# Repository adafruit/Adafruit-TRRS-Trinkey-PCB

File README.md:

## Adafruit TRRS Trinkey - USB Key for Assistive Technology PCB

<a href="http://www.adafruit.com/products/5954"><br/>
Click here to purchase one from the Adafruit shop</a>

PCB files for the Adafruit TRRS Trinkey - USB Key for Assistive Technology. 

Format is EagleCAD schematic and board layout
* https://www.adafruit.com/product/5954

### Description

It's half USB Key, half TRRS breakout... it's the Adafruit TRRS Trinkey specifically designed for Assistive Technology hackers and creators as a simple and low cost, but also flexible and extendable AT device. 

Many AT interface devices use 3.5mm audio jacks to create switches or variable inputs - often mono TS or stereo TRS plugs. On the TRRS Trinkey, we connect all 6 pins of a 'switched' TRRS jack - tip, ring 1, ring 2, sleeve and the tip switch plus ring 1 switch - to 6 GPIO pins on the microcontroller. That means we can not only detect when plugs are inserted but can change which pins are input, ground or even 3V power. With the use of a stereo/mic splitter, we can have up to 3 simple switches, or two analog potentiometers, or one of each! We particularly like this jack because it has two through-hole contacts near the opening for a good mechanical connection.

The PCB is designed to plug into any USB A port on a computer or laptop. There's an ATSAMD21 microcontroller on board with just enough circuitry to keep it happy. One pin of the microcontroller connects to a NeoPixel LED. A reset button lets you enter bootloader mode if necessary. The microcontroller can be programmed easily thanks to the UF2 bootloader and CircuitPython: simply drag-n-drop new code on.

The SAMD21 can run CircuitPython or Arduino nicely. Over the USB connection, you can have serial, MIDI, or HID keyboard/mouse connectivity. Because its a fully programmable chip, it's possible to customize the keyboard or mouse commands executed on each button, or even set up chording patterns.

Features:

* ATSAMD21E18 32-bit Cortex M0+ - 48 MHz 32-bit processor with 256KB Flash and 32 KB RAM
* Native USB supported by every OS - can be used in Arduino or CircuitPython as a USB serial console, MIDI, Keyboard/Mouse HID, and even a little disk drive for storing Python scripts. Can act like a keyboard to phones or tablets with a USB adapter cable.
* Can be used with Arduino IDE or CircuitPython
* TRRS Jack with two switches on tip and ring 1. All 6 contacts connect to analog-input capable GPIO pins
* One RGB NeoPixel LED
* STEMMA QT port with JST SH 4-pin compatible connector - can be used to add I2C devices, or two more inputs. Note CircuitPython may not have enough memory for large chip drivers.
* Reset switch to start your project code over or enter bootloader mode
* Open Source Hardware so you have full control over your assistive tech!

### License

Adafruit invests time and resources providing this open source design, please support Adafruit and open-source hardware by purchasing products from [Adafruit](https://www.adafruit.com)!

Designed by Limor Fried/Ladyada for Adafruit Industries.

Creative Commons Attribution/Share-Alike, all text above must be included in any redistribution. 
See license.txt for additional details.

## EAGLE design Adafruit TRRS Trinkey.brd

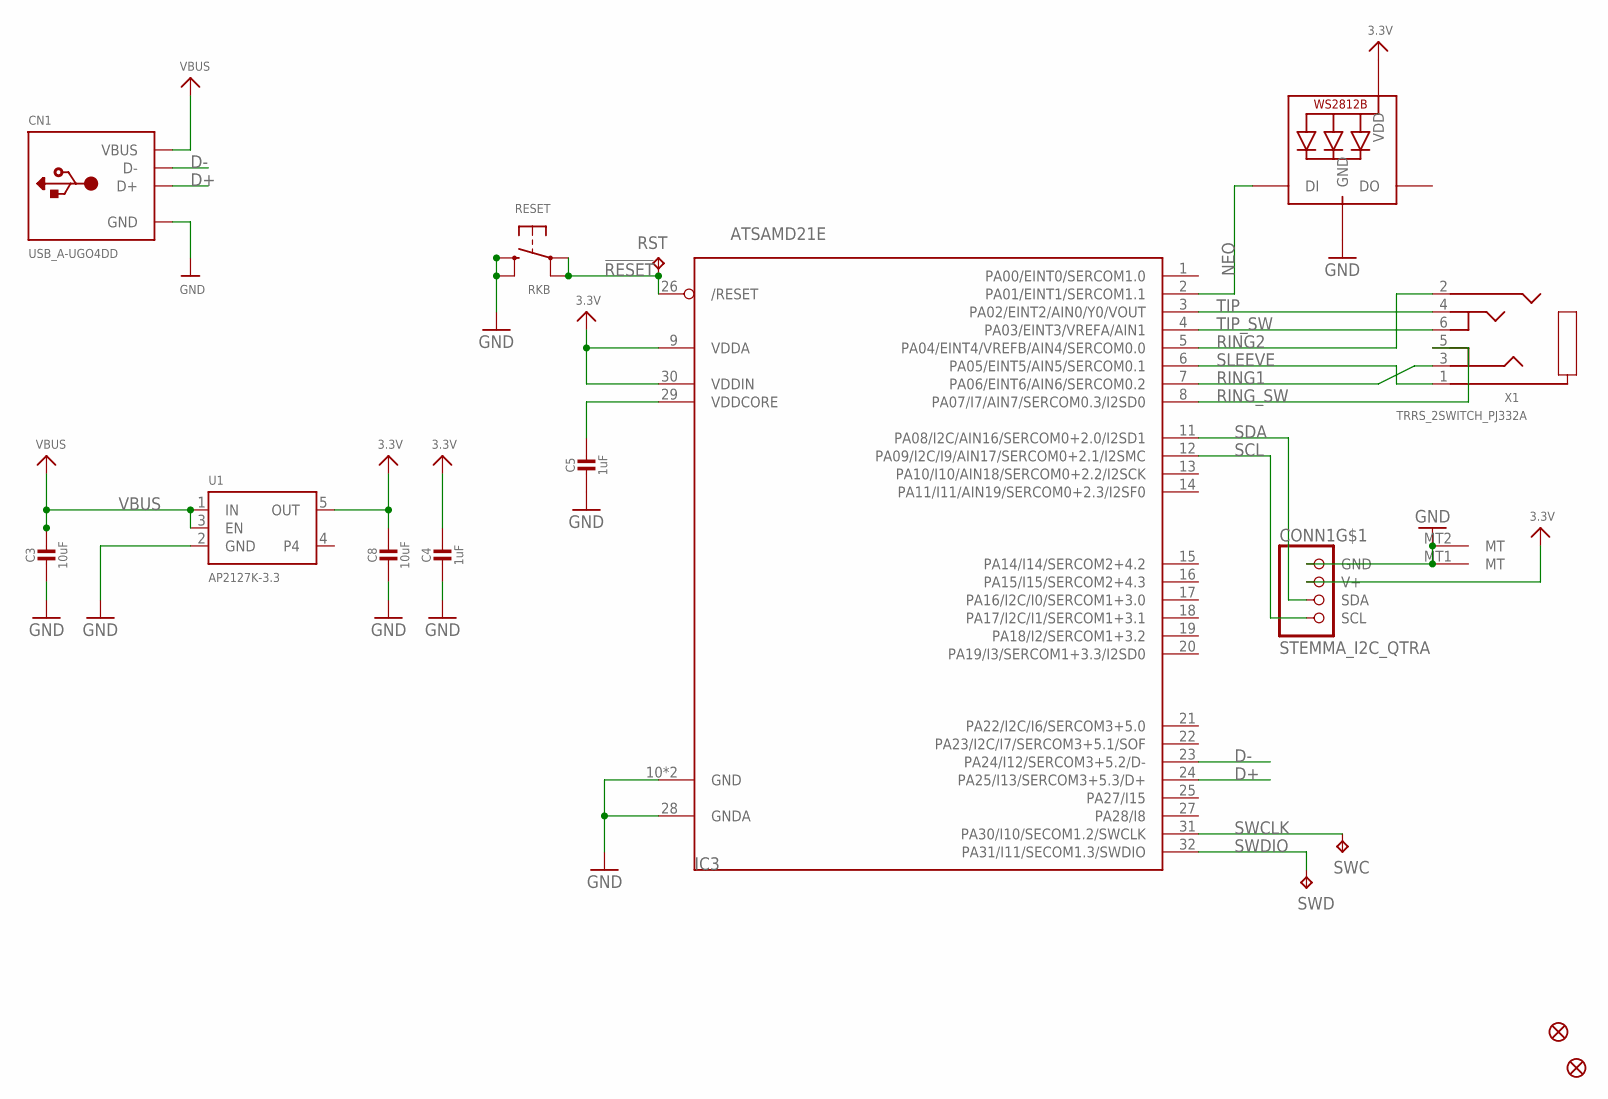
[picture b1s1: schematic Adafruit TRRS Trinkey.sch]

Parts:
C3, C8: 10uF; 0805-NO
C4, C5: 1uF; 0603-NO
CN1: USB_A-UGO4DD
CONN1: STEMMA_I2C_QTRA; JST_SH4_RA
FID1, FID2: FIDUCIAL_0.5MM
IC3: ATSAMD21E; QFN32_5MM
LED1: WS2812B_SK6805_1515; SK6805_1515
RESET: RKB; BTN_RKB2_4.6X2.8
RST: TPTP16R; TP16R
SWC: TPTP15R; TP15R
SWD: TPTP16R; TP16R
U1: AP2127K-3.3; SOT23-5; JLC_ROTATION 0
X1: TRRS_2SWITCH_PJ332A; PJ-332A

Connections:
3.3V: C4.1, C8.1, CONN1.2 (V+), IC3.9 (VDDA), IC3.30 (VDDIN), LED1.2 (VDD), U1.5 (OUT)
!RESET: IC3.26 (/RESET), RESET.A, RESET.A' (P1), RST.TP
D+: CN1.D+, IC3.24 (PA25/I13/SERCOM3+5.3/D+)
D-: CN1.D-, IC3.23 (PA24/I12/SERCOM3+5.2/D-)
GND: C3.2, C4.2, C5.2, C8.2, CN1.GND, CONN1.1 (GND), CONN1.MT1 (MT), CONN1.MT2 (MT), IC3.10 (GND), IC3.28 (GNDA), IC3.33 (GND), LED1.4 (GND), RESET.B (S), RESET.B' (S1), U1.2 (GND)
NEO: IC3.2 (PA01/EINT1/SERCOM1.1), LED1.1 (DI)
RING1: IC3.7 (PA06/EINT6/AIN6/SERCOM0.2), X1.3 (RING2)
RING2: IC3.5 (PA04/EINT4/VREFB/AIN4/SERCOM0.0), X1.2 (RING1)
RING_SW: IC3.8 (PA07/I7/AIN7/SERCOM0.3/I2SD0), X1.5 (R2_SW)
SCL: CONN1.4 (SCL), IC3.12 (PA09/I2C/I9/AIN17/SERCOM0+2.1/I2SMC)
SDA: CONN1.3 (SDA), IC3.11 (PA08/I2C/AIN16/SERCOM0+2.0/I2SD1)
SLEEVE: IC3.6 (PA05/EINT5/AIN5/SERCOM0.1), X1.1 (RING)
SWCLK: IC3.31 (PA30/I10/SECOM1.2/SWCLK), SWC.TP
SWDIO: IC3.32 (PA31/I11/SECOM1.3/SWDIO), SWD.TP
TIP: IC3.3 (PA02/EINT2/AIN0/Y0/VOUT), X1.4 (TIP)
TIP_SW: IC3.4 (PA03/EINT3/VREFA/AIN1), X1.6 (TIP_SW)
VBUS: C3.1, CN1.VBUS, U1.1 (IN), U1.3 (EN)
VDDCORE1: C5.1, IC3.29 (VDDCORE)

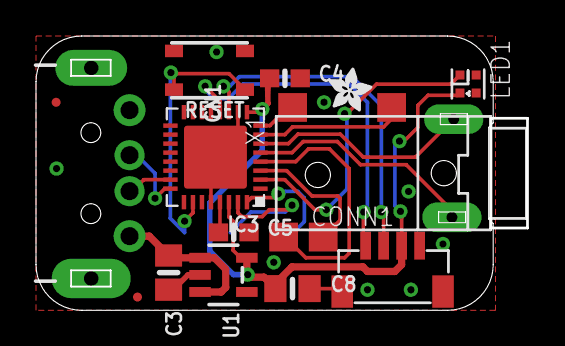
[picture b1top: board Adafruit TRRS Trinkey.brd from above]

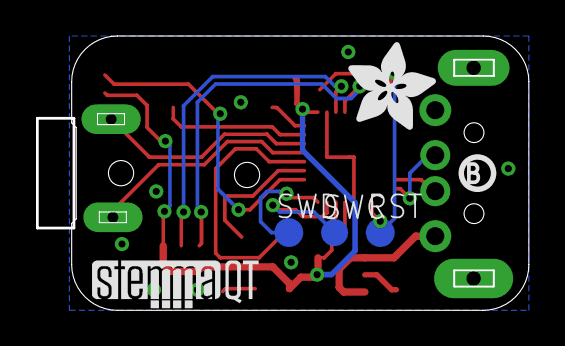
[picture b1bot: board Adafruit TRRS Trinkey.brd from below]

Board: 2 copper layers, 27.2 x 15.1 mm, 28 parts (10 on the bottom side), 18 nets.

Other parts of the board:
PLABEL4: PLABEL4
PLABEL5: PLABEL5
PLABEL6: PLABEL6
PLABEL9: PLABEL9
PLABEL10: PLABEL10
PLABEL11: PLABEL11
PLABEL12: PLABEL12
PLABEL13: PLABEL13
U$4: ADAFRUIT_2.5MM
U$5: STEMMAQT
U$7: ADAFRUIT_5MM
U$8: PCBFEAT-REV-040

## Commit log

2024-05-16 cookiecutter
2024-05-17 prettypins
2024-05-28 prettypins update

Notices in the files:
parts and their libraries:
microbuilder: This work is placed in the public domain, and may be freely used for commercial and non-commercial work with the following conditions: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
